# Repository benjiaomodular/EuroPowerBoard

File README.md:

# EuroPowerBoard
[![CC BY-SA 4.0][cc-by-sa-shield]][cc-by-sa]

This is a busboard for Eurorack synths but with a modification for my own builds.

Version 1 supports 10-pin IDC/Eurorack power connectors.
Version 2 supports 16-pin IDC and 4-pin JST power connectors.

Learn more about it on my website: https://benjiaomodular.com/post/2024-04-09-europowerboard-v2/

Project was sponsored by PCBWay. Order directly from [their website](https://www.pcbway.com/project/shareproject/EuroPowerBoard_v2_db65723e.html). 

# License

This work is licensed under a
[Creative Commons Attribution-ShareAlike 4.0 International License][cc-by-sa].

[![CC BY-SA 4.0][cc-by-sa-image]][cc-by-sa]

[cc-by-sa]: http://creativecommons.org/licenses/by-sa/4.0/
[cc-by-sa-image]: https://licensebuttons.net/l/by-sa/4.0/88x31.png
[cc-by-sa-shield]: https://img.shields.io/badge/License-CC%20BY--SA%204.0-lightgrey.svg

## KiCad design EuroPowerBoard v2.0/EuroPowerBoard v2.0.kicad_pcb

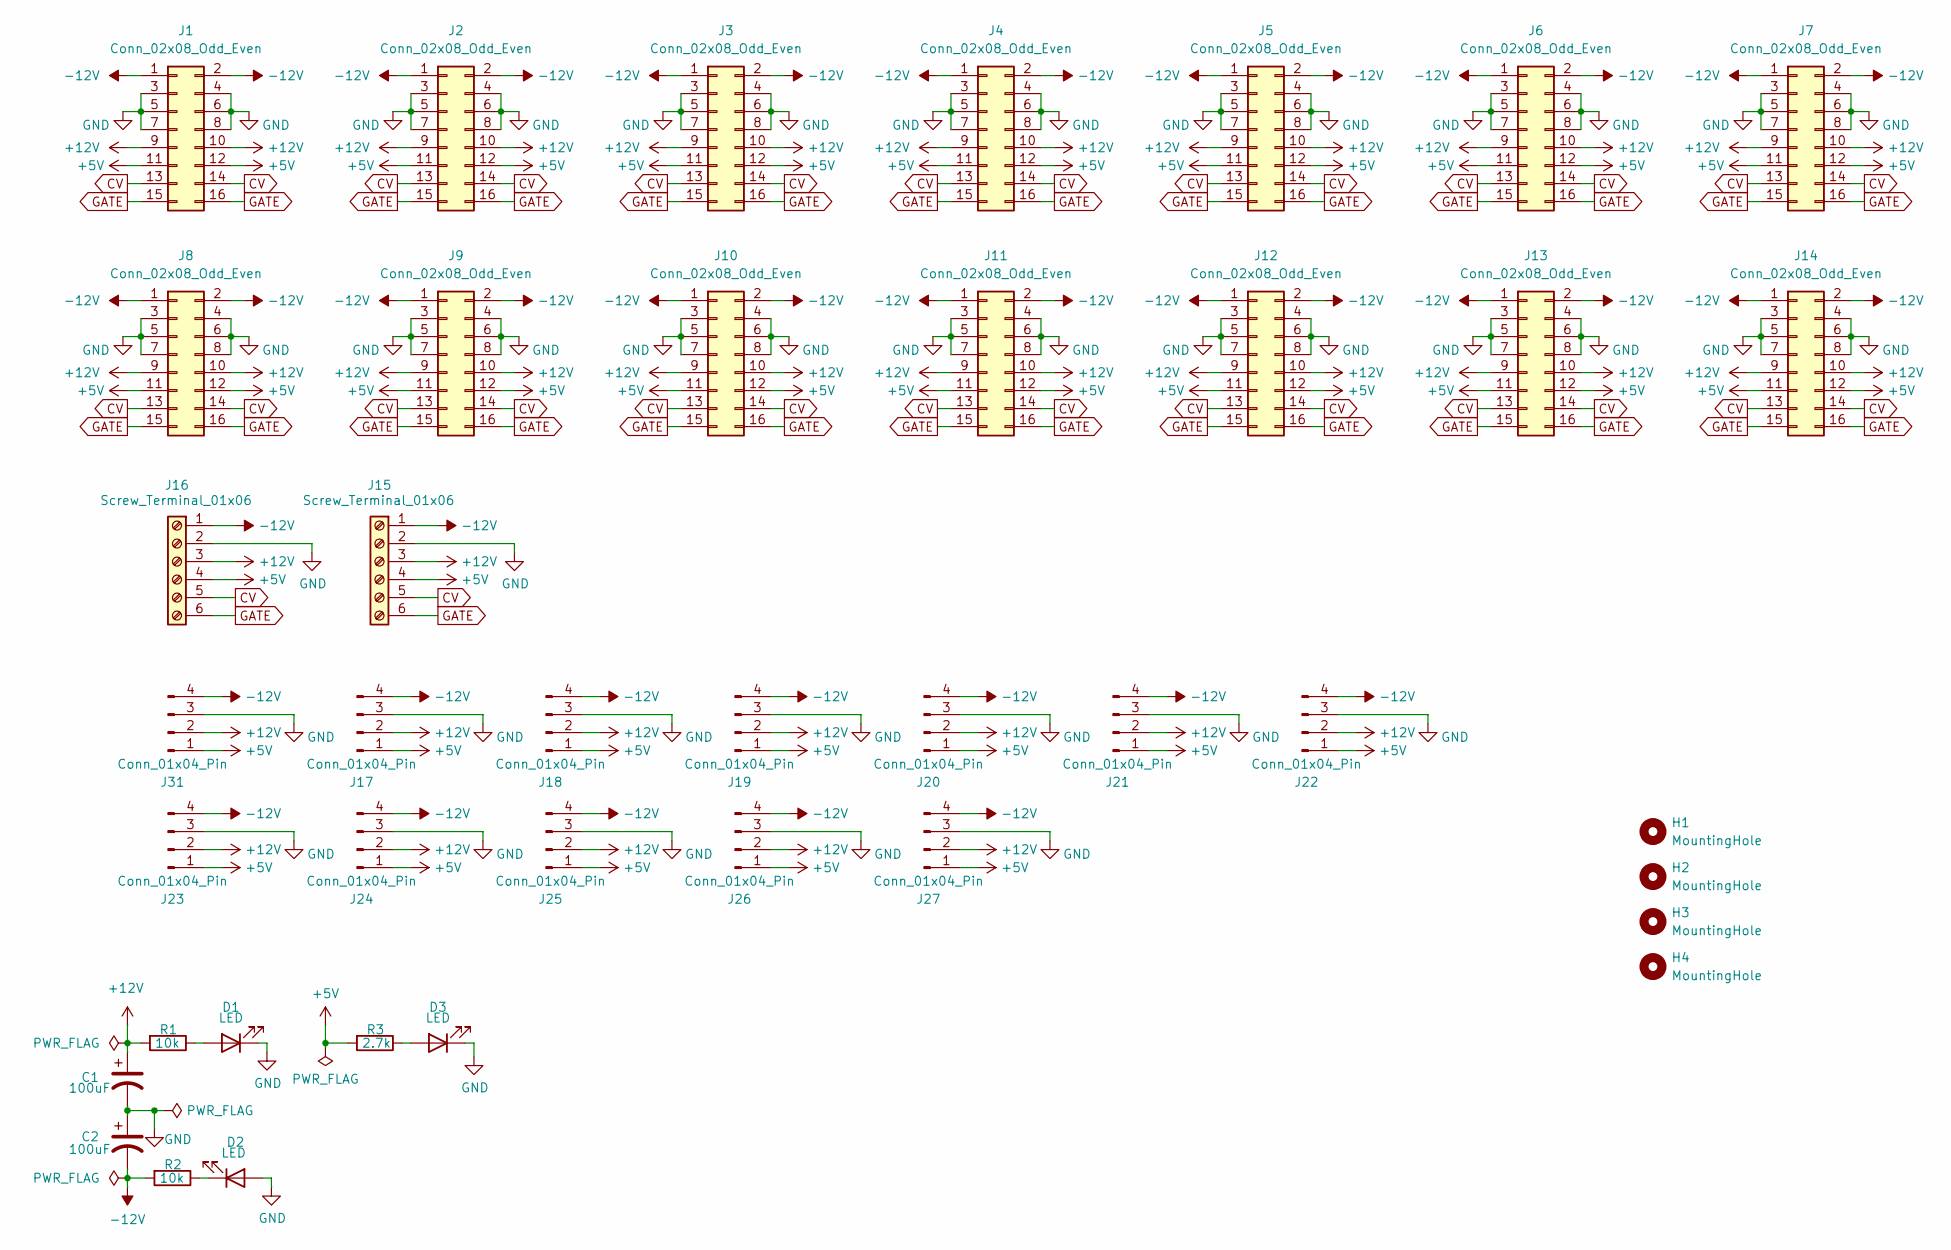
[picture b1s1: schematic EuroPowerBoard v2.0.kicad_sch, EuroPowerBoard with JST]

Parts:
C1, C2: 100uF; CP_Radial_D5.0mm_P2.50mm; Manufacturers Part Numb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 ESH107M010AC3AA
D1, D2, D3: LED; LED_0805_2012Metric_Pad1.15x1.40mm_HandSolder; Manufacturers Part Numb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 EL304RD; LCSC Part # C2856645
H1, H2, H3, H4: MountingHole; MountingHole_4.3mm_M4_ISO7380_Pad
J1, J2, J3, J4, J5, J6, J7, J8, J9, J10, J11, J12, J13, J14: Conn_02x08_Odd_Even; IDC-Header_2x08_P2.54mm_Vertical
J15, J16: Screw_Terminal_01x06; TerminalBlock_RND_205-00005_1x06_P5.00mm_Horizontal
J17, J18, J19, J20, J21, J22, J23, J24, J25, J26, J27, J31: Conn_01x04_Pin; JST_XH_B4B-XH-A_1x04_P2.50mm_Vertical
R1, R2: 10k; R_0603_1608Metric_Pad0.98x0.95mm_HandSolder; Mfg # AC0603FR-0710KL; LCSC Part # C116677
R3: 2.7k; R_0603_1608Metric_Pad0.98x0.95mm_HandSolder; Mfg # AC0603FR-0710KL; LCSC Part # C116677

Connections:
+5V: J1.11, J1.12, J2.11, J2.12, J3.11, J3.12, J4.11, J4.12, J5.11, J5.12, J6.11, J6.12, J7.11, J7.12, J8.11, J8.12, J9.11, J9.12, J10.11, J10.12, J11.11, J11.12, J12.11, J12.12, J13.11, J13.12, J14.11, J14.12, J15.4, J16.4, J17.1, J18.1, J19.1, J20.1, J21.1, J22.1, J23.1, J24.1, J25.1, J26.1, J27.1, J31.1, R3.2
+12V: C1.1, J1.9, J1.10, J2.9, J2.10, J3.9, J3.10, J4.9, J4.10, J5.9, J5.10, J6.9, J6.10, J7.9, J7.10, J8.9, J8.10, J9.9, J9.10, J10.9, J10.10, J11.9, J11.10, J12.9, J12.10, J13.9, J13.10, J14.9, J14.10, J15.3, J16.3, J17.2, J18.2, J19.2, J20.2, J21.2, J22.2, J23.2, J24.2, J25.2, J26.2, J27.2, J31.2, R1.2
-12V: C2.2, J1.1, J1.2, J2.1, J2.2, J3.1, J3.2, J4.1, J4.2, J5.1, J5.2, J6.1, J6.2, J7.1, J7.2, J8.1, J8.2, J9.1, J9.2, J10.1, J10.2, J11.1, J11.2, J12.1, J12.2, J13.1, J13.2, J14.1, J14.2, J15.1, J16.1, J17.4, J18.4, J19.4, J20.4, J21.4, J22.4, J23.4, J24.4, J25.4, J26.4, J27.4, J31.4, R2.2
CV: J1.13, J1.14, J2.13, J2.14, J3.13, J3.14, J4.13, J4.14, J5.13, J5.14, J6.13, J6.14, J7.13, J7.14, J8.13, J8.14, J9.13, J9.14, J10.13, J10.14, J11.13, J11.14, J12.13, J12.14, J13.13, J13.14, J14.13, J14.14, J15.5, J16.5
GATE: J1.15, J1.16, J2.15, J2.16, J3.15, J3.16, J4.15, J4.16, J5.15, J5.16, J6.15, J6.16, J7.15, J7.16, J8.15, J8.16, J9.15, J9.16, J10.15, J10.16, J11.15, J11.16, J12.15, J12.16, J13.15, J13.16, J14.15, J14.16, J15.6, J16.6
GND: C1.2, C2.1, D1.1 (K), D2.2 (A), D3.1 (K), J1.3, J1.4, J1.5, J1.6, J1.7, J1.8, J2.3, J2.4, J2.5, J2.6, J2.7, J2.8, J3.3, J3.4, J3.5, J3.6, J3.7, J3.8, J4.3, J4.4, J4.5, J4.6, J4.7, J4.8, J5.3, J5.4, J5.5, J5.6, J5.7, J5.8, J6.3, J6.4, J6.5, J6.6, J6.7, J6.8, J7.3, J7.4, J7.5, J7.6, J7.7, J7.8, J8.3, J8.4, J8.5, J8.6, J8.7, J8.8, J9.3, J9.4, J9.5, J9.6, J9.7, J9.8, J10.3, J10.4, J10.5, J10.6, J10.7, J10.8, J11.3, J11.4, J11.5, J11.6, J11.7, J11.8, J12.3, J12.4, J12.5, J12.6, J12.7, J12.8, J13.3, J13.4, J13.5, J13.6, J13.7, J13.8, J14.3, J14.4, J14.5, J14.6, J14.7, J14.8, J15.2, J16.2, J17.3, J18.3, J19.3, J20.3, J21.3, J22.3, J23.3, J24.3, J25.3, J26.3, J27.3, J31.3
unnamed: D1.2 (A), R1.1
unnamed: D2.1 (K), R2.1
unnamed: D3.2 (A), R3.1

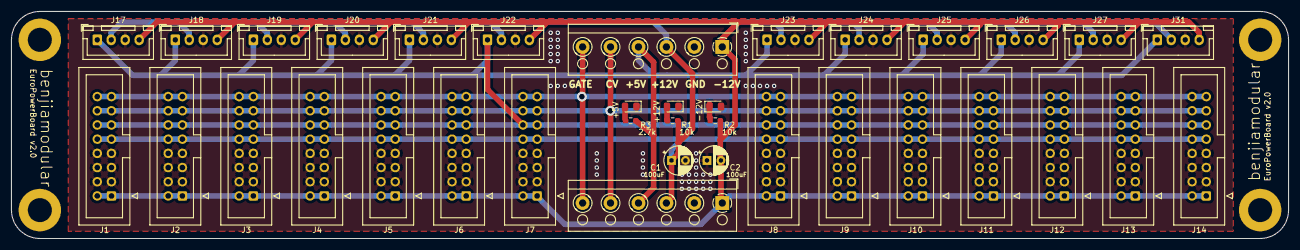
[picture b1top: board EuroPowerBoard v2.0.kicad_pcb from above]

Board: 2 copper layers, 228.6 x 40.6 mm, 40 parts (0 on the bottom side), 9 nets.

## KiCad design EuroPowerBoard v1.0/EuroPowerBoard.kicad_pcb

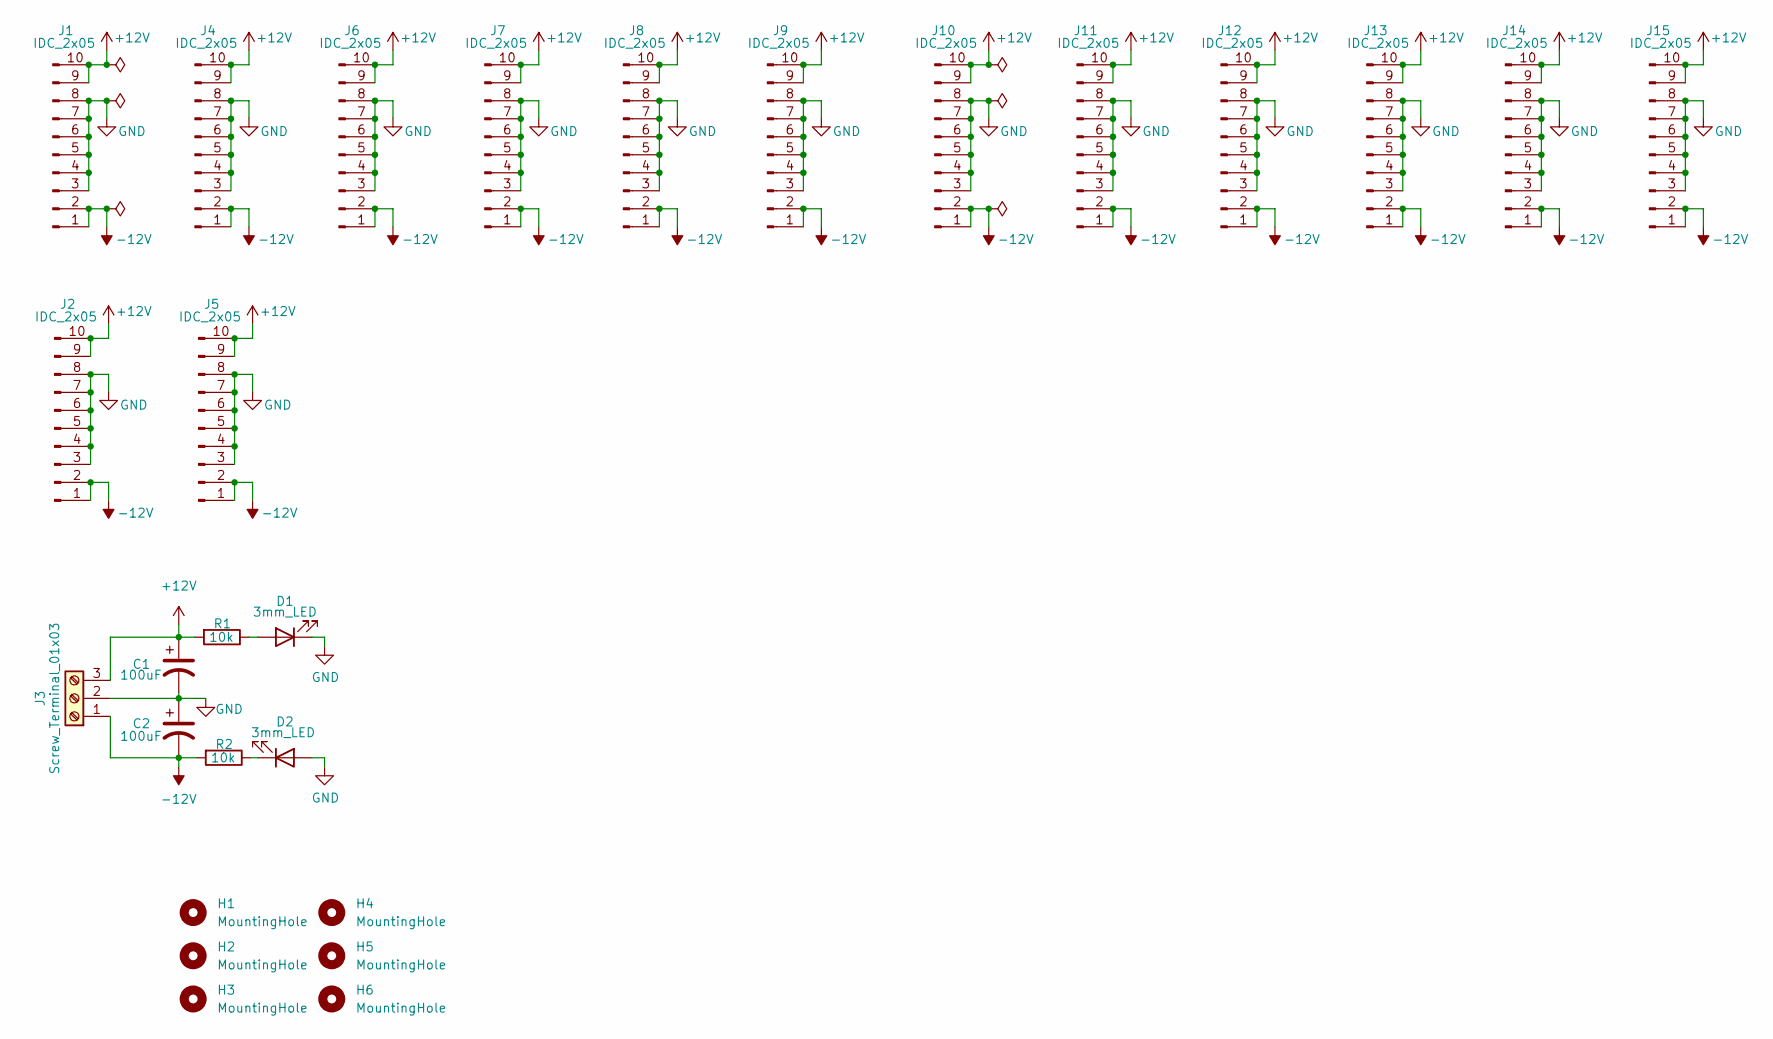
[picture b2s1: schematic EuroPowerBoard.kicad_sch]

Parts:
C1, C2: 100uF; Capacitor_Radial_D5.0mm_P2.5mm; Manufacturers Part Numb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 ESH107M010AC3AA
D1, D2: 3mm_LED; LED_0805_2012Metric_Pad1.15x1.40mm_HandSolder; Manufacturers Part Numb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 EL304RD; LCSC Part # C2856645
H1, H2, H3, H4, H5, H6: MountingHole; MountingHole_3.2mm_M3_DIN965_Pad_TopBottom
J1, J2, J4, J5, J6, J7, J8, J9, J10, J11, J12, J13, J14, J15: IDC_2x05; IDC-Header_2x05_P2.54mm_Vertical; Manufacturers Part Numb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 X9555WV-2X05-6TV01; LCSC Part # C706914
J3: Screw_Terminal_01x03; TerminalBlock_Altech_AK300-3_P5.00mm; Manufacturers Part Numb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 AK300/3
R1, R2: 10k; R_0603_1608Metric_Pad0.98x0.95mm_HandSolder; Mfg # AC0603FR-0710KL; LCSC Part # C116677

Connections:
+12V: C1.1, J1.9, J1.10, J2.9, J2.10, J3.3, J4.9, J4.10, J5.9, J5.10, J6.9, J6.10, J7.9, J7.10, J8.9, J8.10, J9.9, J9.10, J10.9, J10.10, J11.9, J11.10, J12.9, J12.10, J13.9, J13.10, J14.9, J14.10, J15.9, J15.10, R1.2
-12V: C2.2, J1.1, J1.2, J2.1, J2.2, J3.1, J4.1, J4.2, J5.1, J5.2, J6.1, J6.2, J7.1, J7.2, J8.1, J8.2, J9.1, J9.2, J10.1, J10.2, J11.1, J11.2, J12.1, J12.2, J13.1, J13.2, J14.1, J14.2, J15.1, J15.2, R2.2
GND: C1.2, C2.1, D1.1 (K), D2.2 (A), J1.3, J1.4, J1.5, J1.6, J1.7, J1.8, J2.3, J2.4, J2.5, J2.6, J2.7, J2.8, J3.2, J4.3, J4.4, J4.5, J4.6, J4.7, J4.8, J5.3, J5.4, J5.5, J5.6, J5.7, J5.8, J6.3, J6.4, J6.5, J6.6, J6.7, J6.8, J7.3, J7.4, J7.5, J7.6, J7.7, J7.8, J8.3, J8.4, J8.5, J8.6, J8.7, J8.8, J9.3, J9.4, J9.5, J9.6, J9.7, J9.8, J10.3, J10.4, J10.5, J10.6, J10.7, J10.8, J11.3, J11.4, J11.5, J11.6, J11.7, J11.8, J12.3, J12.4, J12.5, J12.6, J12.7, J12.8, J13.3, J13.4, J13.5, J13.6, J13.7, J13.8, J14.3, J14.4, J14.5, J14.6, J14.7, J14.8, J15.3, J15.4, J15.5, J15.6, J15.7, J15.8
unnamed: D1.2 (A), R1.1
unnamed: D2.1 (K), R2.1

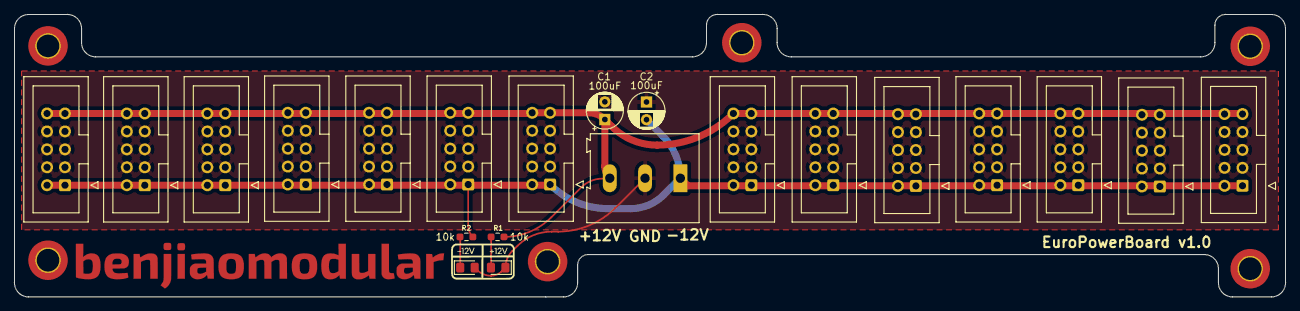
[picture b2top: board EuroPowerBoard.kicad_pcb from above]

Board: 2 copper layers, 180.0 x 40.0 mm, 27 parts (0 on the bottom side), 5 nets.

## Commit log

2024-04-10 Added v2
2024-04-10 updated readme, added license
2024-04-10 Added photo
2024-04-19 Added more links
